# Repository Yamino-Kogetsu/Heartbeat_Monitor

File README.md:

# Heartbeat_Monitor
Using ESP32-C3-WROOM-02 with MAX3010x sensor for monitoring SpO2, heartbeat/heartrate, etc...

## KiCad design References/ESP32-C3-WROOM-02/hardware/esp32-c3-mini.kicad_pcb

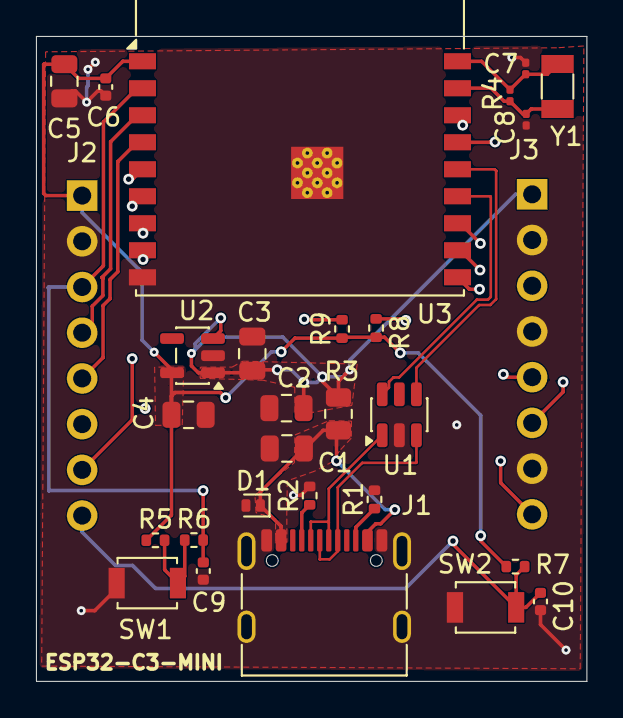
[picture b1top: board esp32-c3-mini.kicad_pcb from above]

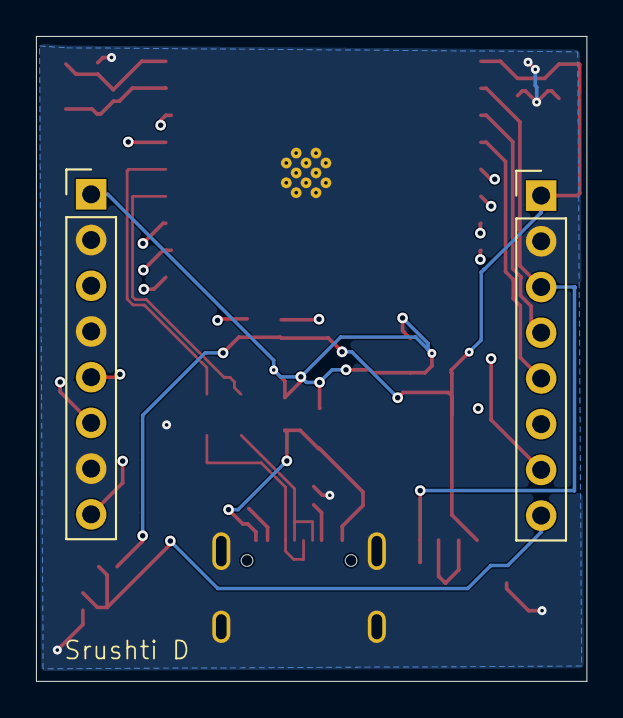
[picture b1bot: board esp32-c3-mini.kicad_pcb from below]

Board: 4 copper layers, 30.6 x 35.8 mm, 29 parts (2 on the bottom side), 25 nets.

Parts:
C1, C2, C3, C4, C5: 4u7; C_0805_2012Metric
C6, C9, C10: 100n; C_0402_1005Metric
C7, C8: TBD; C_0201_0603Metric
D1: PESD5V0L1UL; D_SOD-882D
J1: USB-C; USB_C_Receptacle_G-Switch_GT-USB-7010ASV
J2, J3: 8-pin header; PinHeader_1x08_P2.54mm_Vertical
R1, R2: 5k1; R_0402_1005Metric
R3: 0R; R_0805_2012Metric
R4: TBD; R_0201_0603Metric
R5, R7, R8, R9: 10k; R_0402_1005Metric
R6: 100k; R_0402_1005Metric
SW1, SW2: Push Button; SW_SPST_B3U-1000P
U1: USB-UART IC; SOT-23-6
U2: AP2112K-3.3; SOT-23-5
U3: ESP32-C3-WROOM-02
Y1: Crystal; Crystal_SMD_3215-2Pin_3.2x1.5mm

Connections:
+3V3: C4.1, C5.1, C6.1, J2.1, R5.1, R7.1, R8.1, R9.1, U2.5 (VOUT), U3.1 (3V3)
+5V: C2.1, C3.1, J3.1, R3.2, U2.1 (VIN), U2.3 (EN)
/ESP32-C3-MINI/D+: J1.A6 (D+), J1.B6 (D+), U1.3 (I/O2)
/ESP32-C3-MINI/D-: J1.A7 (D-), J1.B7 (D-), U1.1 (I/O1)
EN: C9.1, J2.3, R6.2, U3.2 (EN)
GND: C1.2, C2.2, C3.2, C4.2, C5.2, C6.2, C7.2, C8.2, C9.2, C10.2, D1.2 (A), J1.A1 (GND), J1.A12 (GND), J1.B1 (GND), J1.B12 (GND), J1.SH (SHIELD), J2.2, J3.2, J3.4, J3.7, R1.2, R2.2, SW1.1, SW2.1, U1.2 (GND), U2.2 (GND), U3.9 (GND), U3.19 (GND)
IO2: R8.2, U3.16 (IO2)
IO3: J3.3, U3.15 (IO3)
IO4: J2.4, U3.3 (IO4)
IO5: J2.5, U3.4 (IO5)
IO6: J2.6, U3.5 (IO6)
IO7: J2.7, U3.6 (IO7)
IO8: R9.2, U3.7 (IO8)
IO9: C10.1, J2.8, R7.2, SW2.2, U3.8 (IO9)
IO10: J3.8, U3.10 (IO10)
unnamed: J1.A5 (CC1), R2.1
unnamed: J1.B5 (CC2), R1.1
unnamed: R5.2, R6.1, SW1.2
unnamed: C7.1, R4.1, U3.18 (IO0), Y1.1
unnamed: C8.1, R4.2, U3.17 (IO1), Y1.2
RXD: J3.5, U3.11 (IO20/RXD)
TXD: J3.6, U3.12 (IO21/TXD)
USB_D+: U1.4 (I/O2), U3.14 (IO19)
USB_D-: U1.6 (I/O1), U3.13 (IO18)
VBUS: C1.1, D1.1 (K), J1.A4 (VBUS), J1.A9 (VBUS), J1.B4 (VBUS), J1.B9 (VBUS), R3.1
